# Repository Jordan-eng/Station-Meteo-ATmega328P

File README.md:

🌦️ Station Météo Connectée (ATmega328P)

Bienvenue sur le dépôt de ma Station Météo DIY ! Ce projet est basé sur un microcontrôleur ATmega328P et permet de surveiller la température et l'humidité tout en affichant les données localement sur un écran OLED.

🚀 Fonctionnalités

    Mesure précise de la température et de l'humidité via un capteur DHT22.

    Affichage local sur écran OLED 0.96" via le bus I2C.

    Régulation de tension intégrée (LD1117) pour une alimentation via une source DC externe (9V-12V).

    Indicateur LED pour confirmer la mise sous tension.

🛠️ Matériel (BOM)
Composant	Description
MCU	ATmega328P (Microchip)
Capteur	DHT22 (Température & Humidité)
Écran	OLED SSD1306 (128x64)
Alimentation	LD1117S50 (Régulateur 5V)
Cristal	Quartz 16MHz + 2x 22pF
📐 Schéma Électrique

Le projet a été conçu avec KiCad 7. Vous trouverez les fichiers sources dans le dossier /hardware.
Points clés de la conception :

    Protection contre l'inversion de polarité via la diode D1.

    Filtrage de l'alimentation avec des condensateurs électrolytiques et céramiques.

    Résistances de Pull-up nécessaires sur le bus I2C et le capteur DHT.

💻 Logiciel

Le code est écrit en C++/Arduino. Les bibliothèques suivantes sont requises :

    Adafruit_SSD1306 (pour l'écran OLED)

    DHT sensor library (pour le capteur DHT22)

📂 Structure du Dépôt

    📂 hardware/ : Fichiers KiCad (.kicad_sch, .kicad_pcb).

    📂 firmware/ : Code source Arduino/C++.

    📂 assets/ : Images et schémas du projet.
    
    📂 station_meteo.csv : Ficher Bill of materials(BOM) pour les composants 
    
    📂 station_meteo-top-pos.csv : Ficher CPL

🔧 Installation

    Clonez le dépôt : git clone https://github.com/Jordan-eng/-Station-Meteo-Connectee-ATmega328P-/

    Ouvrez le schéma sous KiCad pour visualiser le circuit.

    Flashez l'ATmega328P avec le code fourni dans le dossier firmware.

Prochaines étapes suggérées :

    Ajouter une interface Wi-Fi (ESP8266) pour envoyer les données sur le cloud.

    Concevoir un boîtier 3D sur mesure.

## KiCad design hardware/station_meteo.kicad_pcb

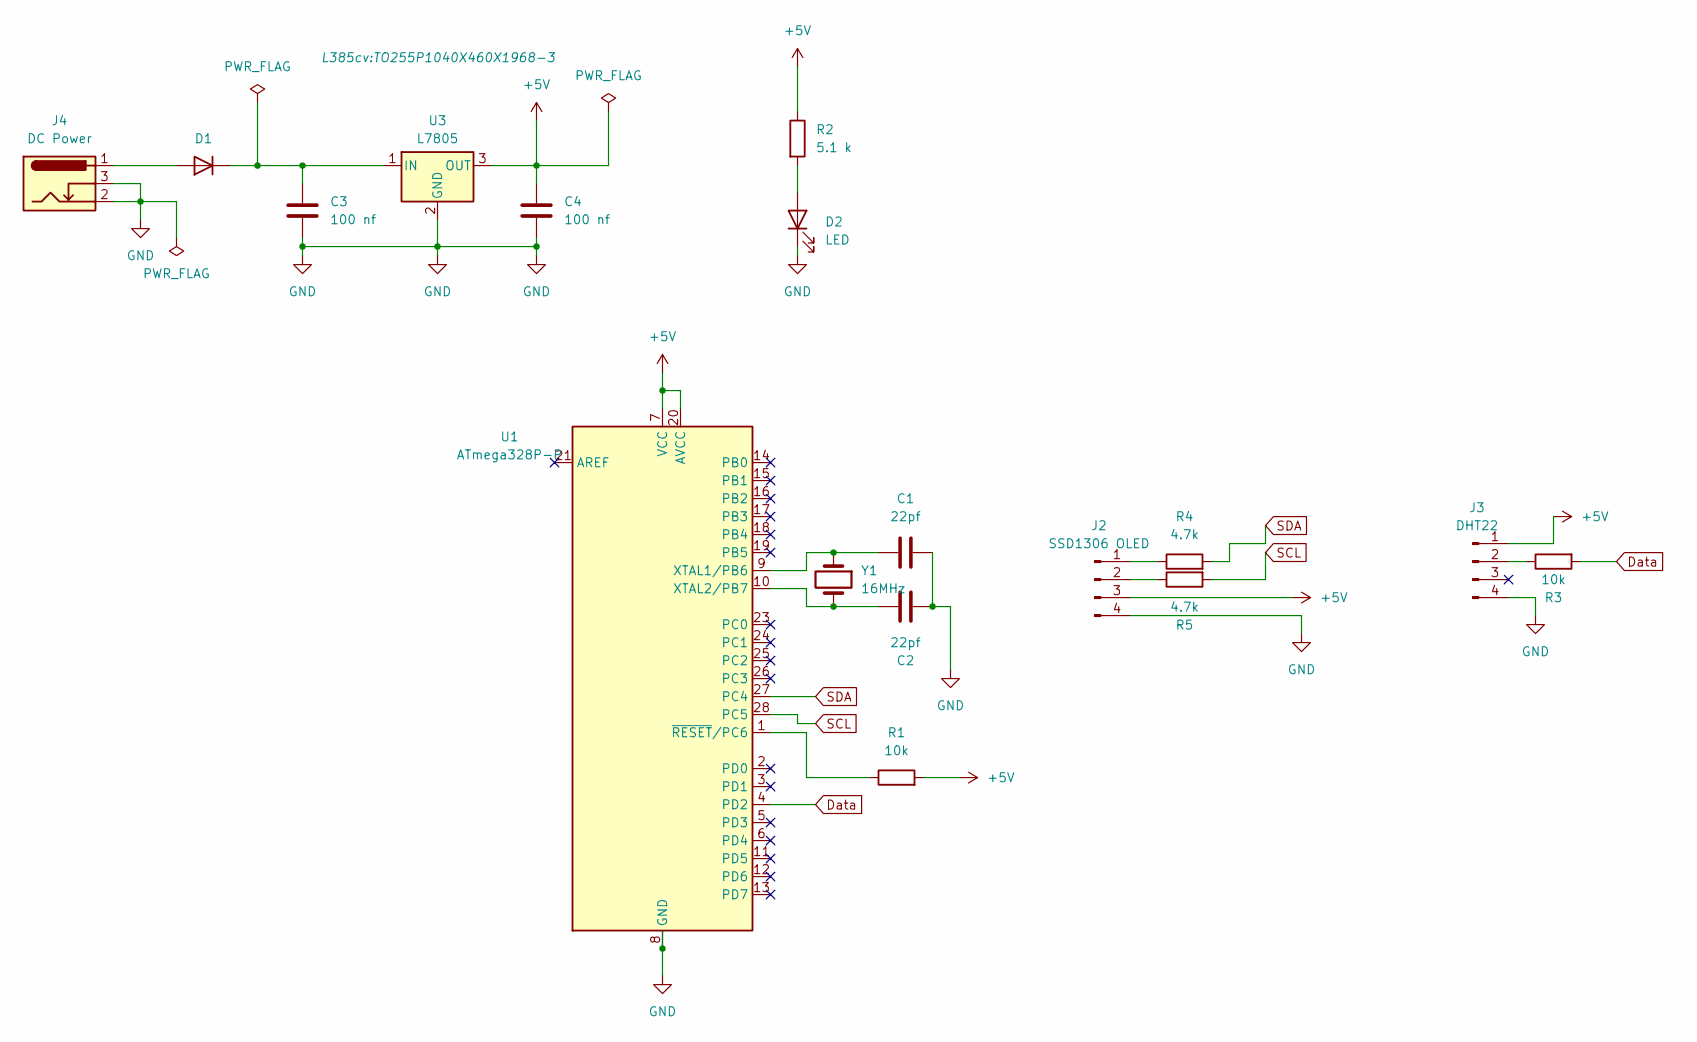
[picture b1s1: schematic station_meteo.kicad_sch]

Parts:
C1, C2: 22pf; C_Disc_D3.4mm_W2.1mm_P2.50mm
C3, C4: 100 nf; C_Disc_D3.4mm_W2.1mm_P2.50mm
D1: Diode; D_DO-41_SOD81_P10.16mm_Horizontal
D2: LED; LED_D3.0mm_Horizontal_O1.27mm_Z2.0mm
J2: SSD1306 OLED; PinHeader_1x04_P2.54mm_Vertical
J3: DHT22; PinHeader_1x04_P2.54mm_Vertical
J4: DC Power; BarrelJack_Horizontal
R1, R3: 10k; R_Axial_DIN0204_L3.6mm_D1.6mm_P5.08mm_Horizontal
R2: 5.1 k; R_Axial_DIN0204_L3.6mm_D1.6mm_P5.08mm_Horizontal
R4, R5: 4.7k; R_Axial_DIN0204_L3.6mm_D1.6mm_P5.08mm_Horizontal
U1: ATmega328P-P; DIP-28_W7.62mm_Socket
U3: L7805; TO255P1040X460X1968-3
Y1: 16MHz; Crystal_HC49-4H_Vertical

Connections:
+5V: C4.1, J2.3, J3.1, R1.2, R2.1, U1.7 (VCC), U1.20 (AVCC), U3.3 (OUT)
Data: R3.2, U1.4 (PD2)
GND: C1.2, C2.1, C3.2, C4.2, D2.1 (K), J2.4, J3.4, J4.2, J4.3, U1.8 (GND), U1.22 (GND), U3.2 (GND)
unnamed: D1.2 (A), J4.1
unnamed: C3.1, D1.1 (K), U3.1 (IN)
unnamed: D2.2 (A), R2.2
unnamed: J2.1, R4.1
unnamed: J2.2, R5.1
unnamed: J3.2, R3.1
unnamed: C1.1, U1.9 (XTAL1/PB6), Y1.1
unnamed: C2.2, U1.10 (XTAL2/PB7), Y1.2
unnamed: R1.1, U1.1 (~RESET/PC6)
SCL: R5.2, U1.28 (PC5)
SDA: R4.2, U1.27 (PC4)

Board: 2 copper layers, 17 parts (0 on the bottom side), 14 nets, no tracks yet.

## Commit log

2026-02-10 Ajout
2026-02-10 Fix repository URL in installation instructions
    Updated repository link for cloning the project.
2026-02-14 Add README for weather station project
    Added detailed project description, features, hardware requirements, software dependencies, repository structure, and installation instructions for the weather station project.
